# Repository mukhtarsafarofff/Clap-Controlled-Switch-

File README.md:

(ENG) The CD4017 IC is a ten-digit decade counter. It has ten outputs that represent the digits 0 through 9. Every rising clock pulse adds one to the counter. It can be used to build a circuit for chasing LEDs. ﻿The condenser mic initially detected the clap sound. The sound is converted into an electric pulse by the condenser microphone. The electric pulse is then amplified by the BC547 transistor. The electrical pulse is then fed to the CD4017 IC's CLK pin. The state of PIN 2 changes with each high pulse at the CLK pin. The second transistor is turned on when PIN 2 becomes HIGH. If the second transistor is turned on, the Relay is activated as well. When the condenser detects the second clap, the next high pulse is received at CLK PIN. PIN 2 changed its state (became LOW), causing the second transistor to turn off. As a result, the relay is turned off, and the load connected to it is also turned off.
(DEU) Der CD4017 IC ist ein zehnstelliger Dekadenzähler. Er hat zehn Ausgänge, die die Ziffern 0 bis 9 darstellen. Jeder ansteigende Taktimpuls erhöht den Zähler um eins. Wenn der Zähler 9 erreicht, setzt der nächste Taktimpuls ihn auf null zurück. Er kann verwendet werden, um eine Schaltung für das Durchlaufen von LEDs zu bauen. Das Kondensatormikrofon hat zunächst das Klatschgeräusch erkannt. Der Schall wird durch das Kondensatormikrofon in einen elektrischen Impuls umgewandelt. Der elektrische Impuls wird dann durch den BC547-Transistor verstärkt. Der elektrische Impuls wird anschließend an den CLK-Pin des CD4017 IC weitergeleitet. Der Zustand von PIN 2 ändert sich bei jedem hohen Impuls am CLK-Pin. Der zweite Transistor wird eingeschaltet, wenn PIN 2 HIGH wird. Wenn der zweite Transistor eingeschaltet ist, wird ebenfalls das Relais aktiviert. Wenn das Kondensatormikrofon den zweiten Klatsch erkennt, wird der nächste hohe Impuls am CLK-PIN empfangen.  PIN 2 änderte seinen Zustand (wurde LOW), was dazu führte, dass der zweite Transistor ausschaltete. Infolgedessen wird das Relais ausgeschaltet und die daran angeschlossene Last ebenfalls abgeschaltet.

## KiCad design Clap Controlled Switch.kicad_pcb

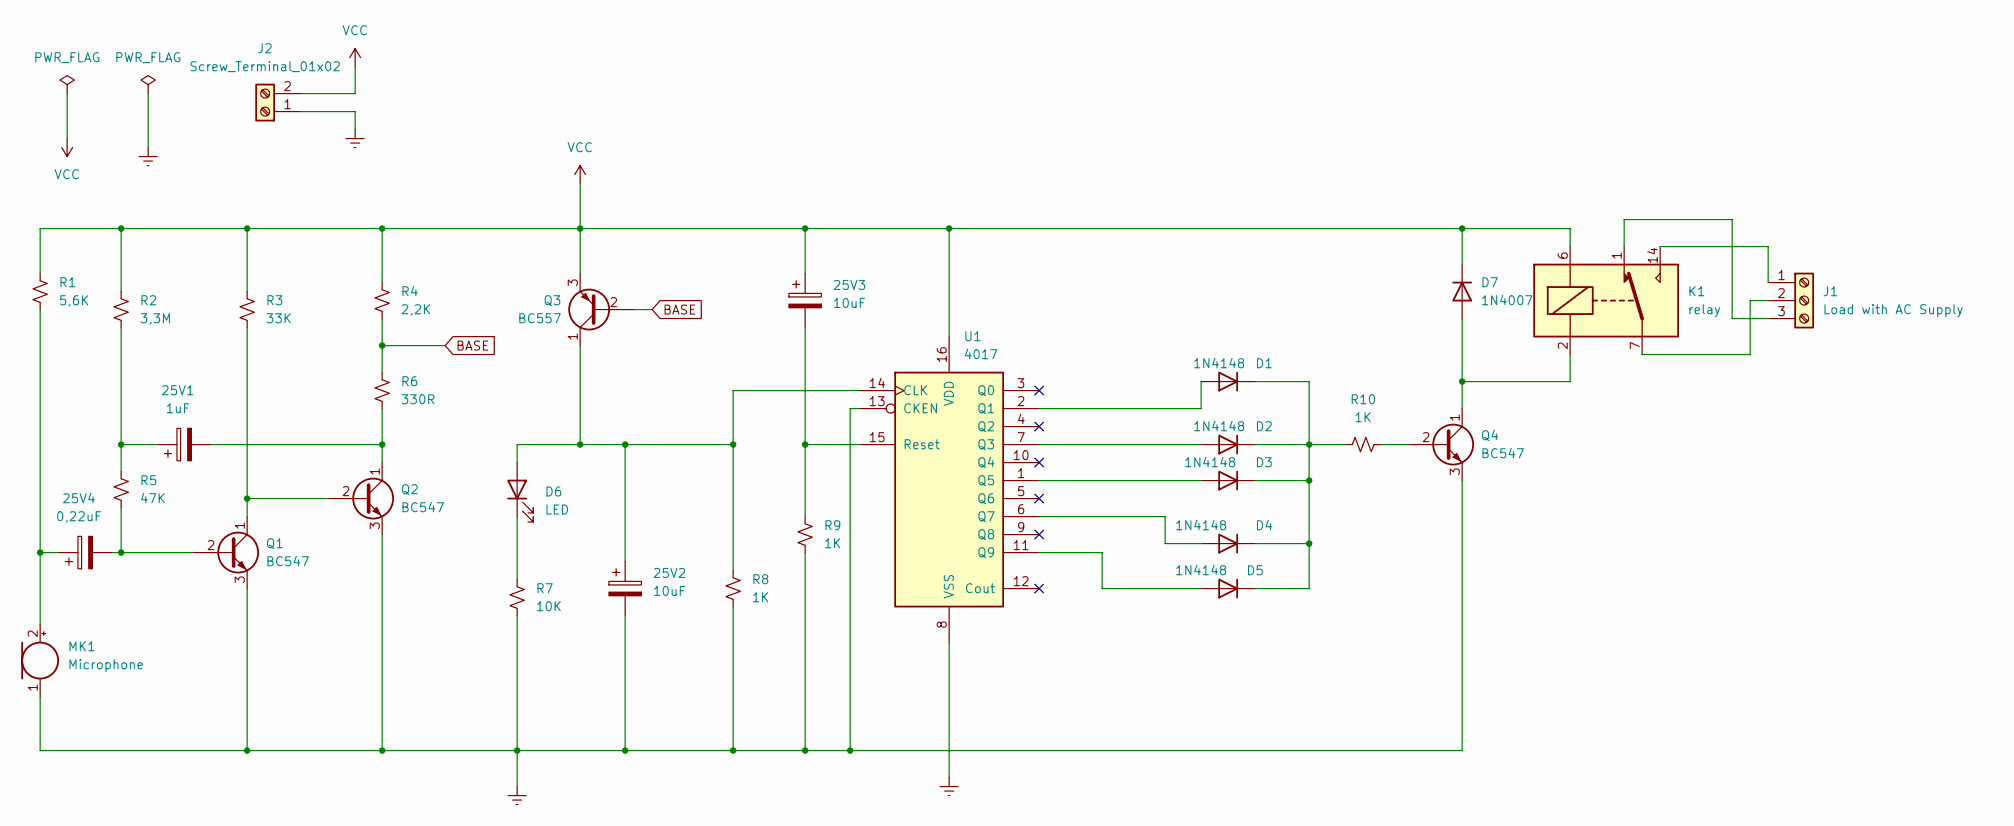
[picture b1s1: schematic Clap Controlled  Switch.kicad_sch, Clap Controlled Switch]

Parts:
25V1: 1uF; CP_Radial_D14.0mm_P7.50mm
25V2, 25V3: 10uF; CP_Radial_D14.0mm_P7.50mm
25V4: 0,22uF; CP_Radial_D14.0mm_P7.50mm
D1, D2, D3, D4, D5: 1N4148; D_DO-35_SOD27_P7.62mm_Horizontal
D6: LED; LED_D5.0mm
D7: 1N4007; D_DO-41_SOD81_P10.16mm_Horizontal
J1: Load with AC Supply; TerminalBlock_bornier-3_P5.08mm
J2: Screw_Terminal_01x02; TerminalBlock_bornier-2_P5.08mm
K1: relay; Relay_StandexMeder_DIP_LowProfile
MK1: Microphone; TerminalBlock_bornier-2_P5.08mm
Q1, Q2, Q4: BC547; TO-92_Inline
Q3: BC557; TO-92_Inline
R1: 5,6K; R_Axial_DIN0309_L9.0mm_D3.2mm_P12.70mm_Horizontal
R2: 3,3M; R_Axial_DIN0309_L9.0mm_D3.2mm_P12.70mm_Horizontal
R3: 33K; R_Axial_DIN0309_L9.0mm_D3.2mm_P12.70mm_Horizontal
R4: 2,2K; R_Axial_DIN0309_L9.0mm_D3.2mm_P12.70mm_Horizontal
R5: 47K; R_Axial_DIN0309_L9.0mm_D3.2mm_P12.70mm_Horizontal
R6: 330R; R_Axial_DIN0309_L9.0mm_D3.2mm_P12.70mm_Horizontal
R7: 10K; R_Axial_DIN0309_L9.0mm_D3.2mm_P12.70mm_Horizontal
R8, R9, R10: 1K; R_Axial_DIN0309_L9.0mm_D3.2mm_P12.70mm_Horizontal
U1: 4017; DIP-16_W7.62mm

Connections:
BASE: Q3.2 (B), R4.2, R6.1
Earth: 25V2.2, J2.1, MK1.1 (-), Q1.3 (E), Q2.3 (E), Q4.3 (E), R7.2, R8.2, R9.2, U1.8 (VSS), U1.13 (CKEN)
unnamed: 25V1.1, R2.2, R5.1
unnamed: D1.2 (A), U1.2 (Q1)
unnamed: D1.1 (K), D2.1 (K), D3.1 (K), D4.1 (K), D5.1 (K), R10.1
unnamed: D2.2 (A), U1.7 (Q3)
unnamed: D3.2 (A), U1.1 (Q5)
unnamed: D4.2 (A), U1.6 (Q7)
unnamed: D5.2 (A), U1.11 (Q9)
unnamed: 25V2.1, D6.2 (A), Q3.1 (C), R8.1, U1.14 (CLK)
unnamed: D6.1 (K), R7.1
unnamed: D7.2 (A), K1.2, Q4.1 (C)
unnamed: J1.1, K1.14
unnamed: J1.2, K1.7, K1.8
unnamed: J1.3, K1.1
unnamed: 25V4.1, MK1.2 (+), R1.2
unnamed: 25V4.2, Q1.2 (B), R5.2
unnamed: Q1.1 (C), Q2.2 (B), R3.2
unnamed: 25V1.2, Q2.1 (C), R6.2
unnamed: Q4.2 (B), R10.2
unnamed: 25V3.2, R9.1, U1.15 (Reset)
VCC: 25V3.1, D7.1 (K), J2.2, K1.6, Q3.3 (E), R1.1, R2.1, R3.1, R4.1, U1.16 (VDD)

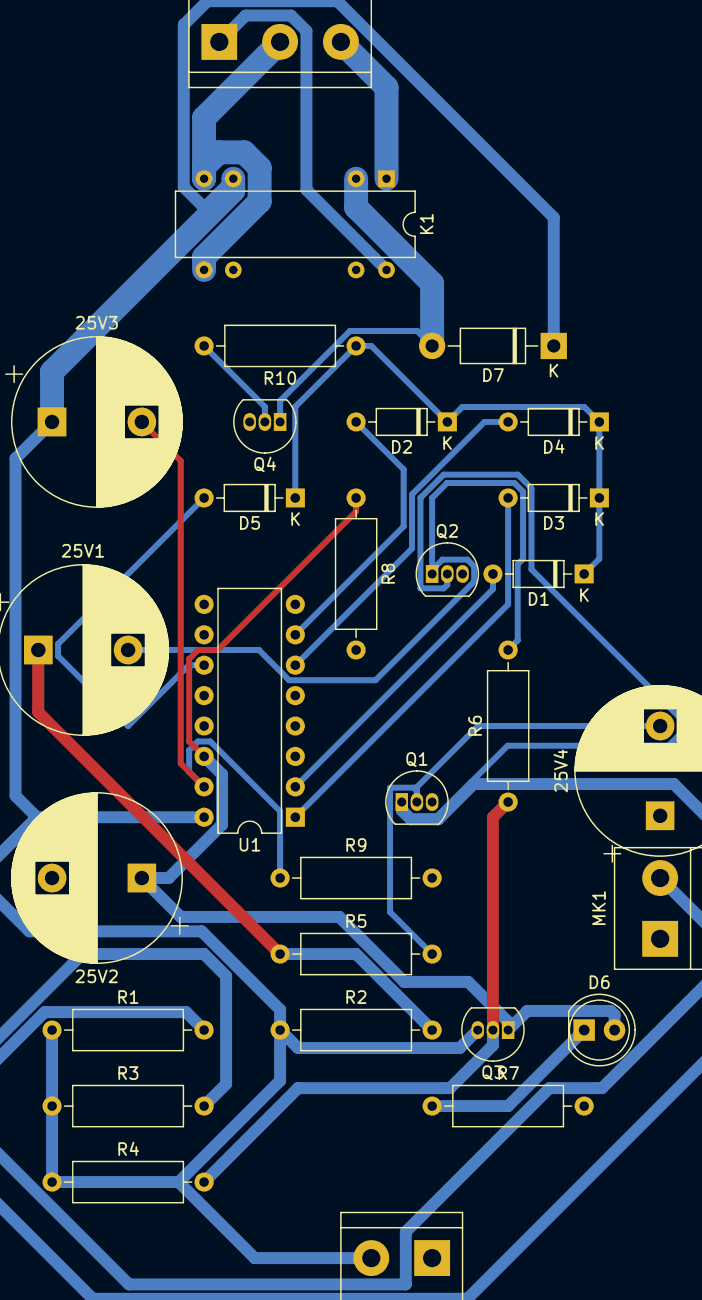
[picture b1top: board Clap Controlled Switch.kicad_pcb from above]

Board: 2 copper layers, 30 parts (0 on the bottom side), 22 nets.

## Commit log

2024-03-23 Clap controlled Switch is accomplished
2024-03-25 Clap Controlled Switch is renewed
